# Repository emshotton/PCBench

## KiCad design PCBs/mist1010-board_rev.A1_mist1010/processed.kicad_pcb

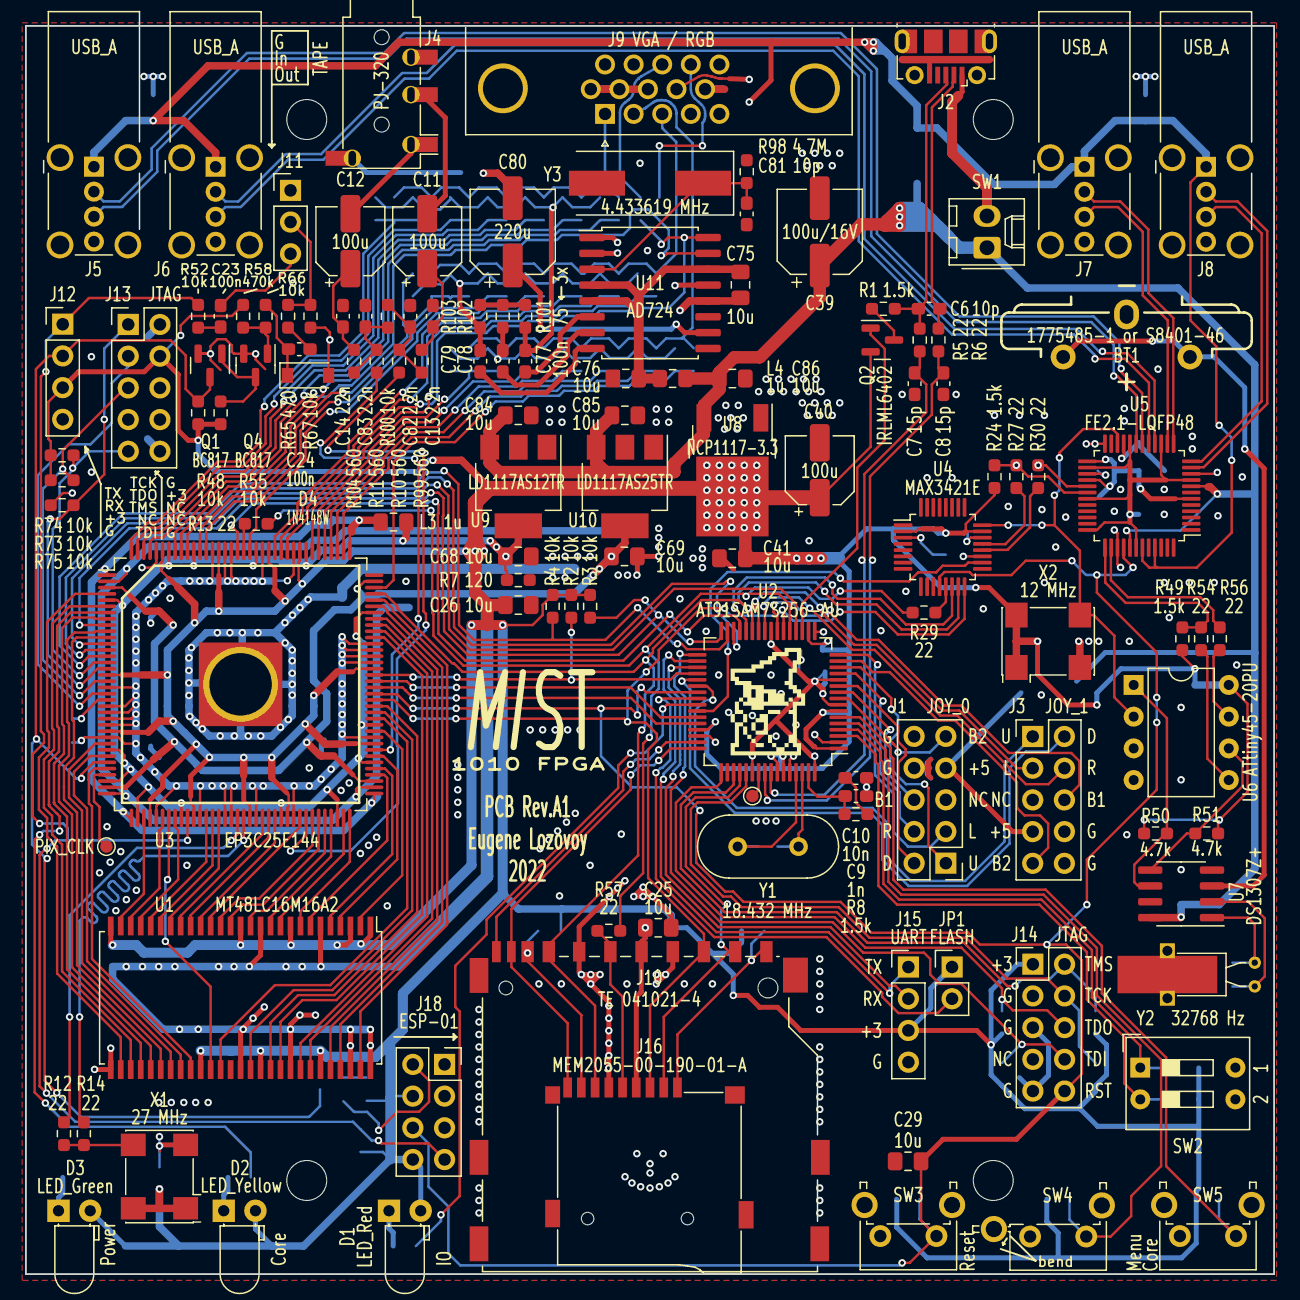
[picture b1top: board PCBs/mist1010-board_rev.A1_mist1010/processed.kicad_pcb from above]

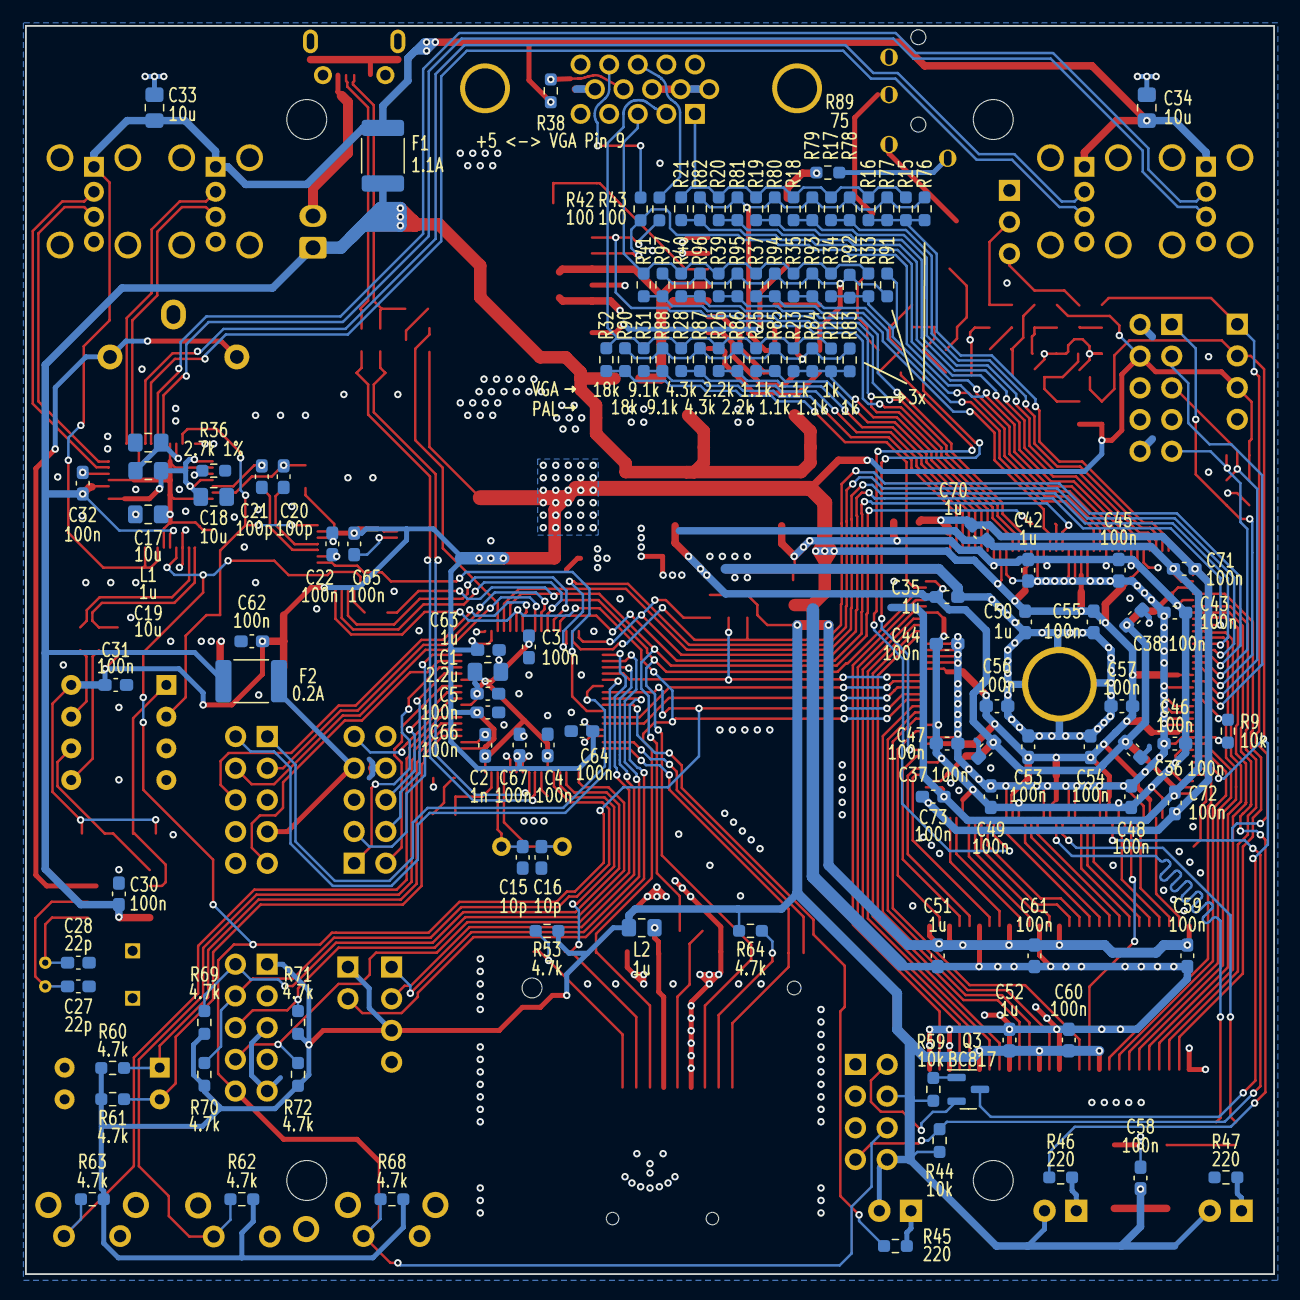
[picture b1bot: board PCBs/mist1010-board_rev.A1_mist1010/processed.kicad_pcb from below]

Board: 2 copper layers, 100.0 x 100.0 mm, 250 parts (123 on the bottom side), 202 nets.

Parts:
BT1: 1775485-1 or S8401-46; CR2032V
C1: 2.2u; C_0805_2012Metric_Pad1.18x1.45mm_HandSolder
C2, C9: 1n; C_0603_1608Metric_Pad1.08x0.95mm_HandSolder
C3, C4, C5, C22, C23, C24, C30, C31, C32, C36, C37, C38, C43, C44, C45, C46, C47, C48, C49, C53, C54, C55, C56, C57, C58, C59, C60, C61, C62, C64, C65, C66, C67, C71, C72, C73, C77, C78, C79: 100n; C_0603_1608Metric_Pad1.08x0.95mm_HandSolder
C6, C15, C16, C81: 10p; C_0603_1608Metric_Pad1.08x0.95mm_HandSolder
C7, C8: 15p; C_0603_1608Metric_Pad1.08x0.95mm_HandSolder
C10: 10n; C_0603_1608Metric_Pad1.08x0.95mm_HandSolder
C11, C12, C40: 100u; CP_Elec_5x5.9
C13, C14, C82, C83: 2.2n; C_0603_1608Metric_Pad1.08x0.95mm_HandSolder
C17, C18, C19, C25, C26, C29, C33, C34, C41, C68, C69, C75, C76, C84, C85, C86: 10u; C_0805_2012Metric_Pad1.18x1.45mm_HandSolder
C20, C21: 100p; C_0603_1608Metric_Pad1.08x0.95mm_HandSolder
C27, C28: 22p; C_0603_1608Metric_Pad1.08x0.95mm_HandSolder
C35, C42, C50, C51, C52, C63, C70: 1u; C_0603_1608Metric_Pad1.08x0.95mm_HandSolder
C39: 100u/16V; CP_Elec_6.3x7.7
C80: 220u; CP_Elec_6.3x7.7
D1: LED_Red; LED_D3.0mm_Horizontal_O1.27mm_Z6.0mm
D2: LED_Yellow; LED_D3.0mm_Horizontal_O1.27mm_Z6.0mm
D3: LED_Green; LED_D3.0mm_Horizontal_O1.27mm_Z6.0mm
D4: 1N4148W; D_SOD-123
F1: 1.1A; Fuse_1812_4532Metric_Pad1.30x3.40mm_HandSolder
F2: 0.2A; Fuse_1812_4532Metric_Pad1.30x3.40mm_HandSolder
H1, H2, H3, H4: Screw M3 dk=5mm L=4mm; MountingHole_3.2mm_M3_dk5.2mm
J1, J3, J13, J14: Conn_02x05_Odd_Even; PinHeader_2x05_P2.54mm_Vertical
J2: USB_B_Micro; USB_Micro-B_Molex-105017-0001
J4: PJ-320; PJ-320A_D
J5, J6, J7, J8: USB_A; USB_A_Wuerth_614004134726_Horizontal
J9: DB15_Female_HighDensity_MountingHoles; DSUB-15-HD_Female_Horizontal_P2.29x1.98mm_EdgePinOffset3.03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
J10: TE 041021-4; SD_TE_2041021-mod
J11: PJ392; PinHeader_1x03_P2.54mm_Vertical
J12, J15: Conn_01x04; PinHeader_1x04_P2.54mm_Vertical
J16: MEM2055-00-190-01-A; GCT-MEM2055-00-190-01-A
J18: ESP-01; PinSocket_2x04_P2.54mm_Vertical
JP1: Jumper_2_Open; PinHeader_1x02_P2.54mm_Vertical
L1, L2, L3, L4: 1u; L_0805_2012Metric_Pad1.15x1.40mm_HandSolder
LOGO1: graphic; black-mage-6.7x9.5
Q1, Q3, Q4: BC817; SOT-23
Q2: IRLML6402; SOT-23
R1, R8, R24, R49: 1.5k; R_0603_1608Metric_Pad0.98x0.95mm_HandSolder
R2, R3, R4, R9, R44, R48, R52, R55, R59, R66, R67, R73, R74, R75, R100: 10k; R_0603_1608Metric_Pad0.98x0.95mm_HandSolder
R5, R6, R12, R13, R14, R27, R29, R30, R54, R56, R57: 22; R_0603_1608Metric_Pad0.98x0.95mm_HandSolder
R7: 120; R_0603_1608Metric_Pad0.98x0.95mm_HandSolder
R10, R11, R99, R104: 560; R_0603_1608Metric_Pad0.98x0.95mm_HandSolder
R15, R22, R33, R76, R83, R91: 1k; R_0603_1608Metric_Pad0.98x0.95mm_HandSolder
R16, R17, R23, R25, R34, R35, R77, R78, R84, R85, R92, R93: 1.1k; R_0603_1608Metric_Pad0.98x0.95mm_HandSolder
R18, R26, R37, R79, R86, R94: 2.2k; R_0603_1608Metric_Pad0.98x0.95mm_HandSolder
R19, R28, R39, R80, R87, R95: 4.3k; R_0603_1608Metric_Pad0.98x0.95mm_HandSolder
R20, R31, R40, R81, R88, R96: 9.1k; R_0603_1608Metric_Pad0.98x0.95mm_HandSolder
R21, R32, R41, R82, R90, R97: 18k; R_0603_1608Metric_Pad0.98x0.95mm_HandSolder
R36: 2.7k 1%; R_0603_1608Metric_Pad0.98x0.95mm_HandSolder
R38: 0; R_0603_1608Metric_Pad0.98x0.95mm_HandSolder
R42, R43: 100; R_0603_1608Metric_Pad0.98x0.95mm_HandSolder
R45, R46, R47: 220; R_0603_1608Metric_Pad0.98x0.95mm_HandSolder
R50, R51, R53, R60, R61, R62, R63, R64, R68, R69, R70, R71, R72: 4.7k; R_0603_1608Metric_Pad0.98x0.95mm_HandSolder
R58: 470k; R_0603_1608Metric_Pad0.98x0.95mm_HandSolder
R65: 470; R_0603_1608Metric_Pad0.98x0.95mm_HandSolder
R89, R101, R102, R103: 75; R_0603_1608Metric_Pad0.98x0.95mm_HandSolder
R98: 4.7M; R_0603_1608Metric_Pad0.98x0.95mm_HandSolder
SW1: PB05A; Molex_KK-254_AE-6410-02A_1x02_P2.54mm_Vertical
SW2: SW_DIP_x02; SW_DIP_SPSTx02_Slide_9.78x7.26mm_W7.62mm_P2.54mm
SW3, SW4, SW5: SW_Push; SW_Tactile_SPST_Angled_PTS645Vx58-2LFS
TP1, TP2: TestPoint; TestPoint_Pad_D1.0mm
U1: MT48LC16M16A2; TSOP-II-54_22.2x10.16mm_P0.8mm
U2: AT91SAM7S256-AU; TQFP-64_10x10mm_P0.5mm
U3: EP3C25E144; ALTERA-QFP-145
U4: MAX3421E; LQFP-32_5x5mm_P0.5mm
U5: FE2.1-LQFP48; LQFP-48_7x7mm_P0.5mm
U6: ATtiny45-20PU; DIP-8_W7.62mm
U7: DS1307Z+; SOIC-8_3.9x4.9mm_P1.27mm
U8: NCP1117-3.3; TO-252-2
U9: LD1117AS12TR; SOT-223-3_TabPin2
U10: LD1117AS25TR; SOT-223-3_TabPin2
U11: AD724; SOIC-16W_7.5x10.3mm_P1.27mm
X1: 27 MHz; Oscillator_SMD_SeikoEpson_SG8002CA-4Pin_7.0x5.0mm
X2: 12 MHz; Oscillator_SMD_SeikoEpson_SG8002CA-4Pin_7.0x5.0mm
Y1: 18.432 MHz; Crystal_HC49-U_Vertical
Y2: 32768 Hz; Crystal_C38-LF_D3.0mm_L8.0mm_Horizontal_1EP_style2
Y3: 4.433619 MHz; Crystal_SMD_HC49-SD

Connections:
+1V2: C42.2, C43.2, C44.2, C45.2, C46.2, C47.2, C48.2, C49.2, C68.2, L3.1, R7.1, U3.5 (VCCINT), U3.29 (VCCINT), U3.34 (VCCINT), U3.38 (VCCINT), U3.45 (VCCINT), U3.61 (VCCINT), U3.70 (VCCINT), U3.78 (VCCINT), U3.84 (VCCINT), U3.102 (VCCINT), U3.116 (VCCINT), U3.124 (VCCINT), U3.134 (VCCINT), U3.138 (VCCINT), U9.2 (VO)
+1V2_PLL: C70.2, C71.2, C72.2, C73.2, L3.2, U3.1 (VCCD_PLL3), U3.37 (VCCD_PLL1), U3.73 (VCCD_PLL4), U3.109 (VCCD_PLL2)
+2V5: C35.2, C36.2, C37.2, C38.2, C69.2, U3.3 (VCCA3), U3.35 (VCCA1), U3.75 (VCCA4), U3.107 (VCCA2), U10.2 (VO)
+3V3: C26.2, C31.2, C40.1, C41.2, C50.2, C51.2, C52.2, C53.2, C54.2, C55.2, C56.2, C57.2, C58.2, C59.2, C60.2, C61.2, C62.2, C63.2, C64.2, C65.2, C66.2, C67.2, D1.2 (A), D2.2 (A), D3.2 (A), J12.3, J13.4, J14.1, J15.3, J18.4, J18.8, JP1.1 (A), L2.1, Q2.2 (S), R2.1, R3.1, R4.1, R24.1, R44.1, R48.2, R49.1, R50.1, R51.1, R53.1, R55.2, R58.2, R59.1, R60.1, R61.1, R62.1, R63.1, R64.1, R68.1, R69.1, R70.1, R71.1, R72.1, R73.1, R74.1, U1.1 (VDD), U1.3 (VDDQ), U1.9 (VDDQ), U1.14 (VDD), U1.27 (VDD), U1.37 (CKE), U1.43 (VDDQ), U1.49 (VDDQ), U2.1 (ADVREF), U2.7 (VDDIN), U2.18 (VDDIO), U2.45 (VDDIO), U2.58 (VDDIO), U2.59 (VDDFLASH), U3.17 (VCCIO1), U3.26 (VCCIO2), U3.40 (VCCIO3), U3.47 (VCCIO3), U3.56 (VCCIO4), U3.62 (VCCIO4), U3.81 (VCCIO5), U3.93 (VCCIO6), U3.117 (VCCIO7), U3.122 (VCCIO7), U3.130 (VCCIO8), U3.139 (VCCIO8), U4.2 (VL), U4.23 (VCC), U6.8 (VCC), U8.2 (VO), X1.1 (EN), X1.4 (V+), X2.1 (EN), X2.4 (V+)
+5V: C30.2, C32.2, C39.1, C84.2, C85.2, C86.2, F1.1, F2.1, L4.1, SW1.1 (A), U5.8 (VDD5), U5.41 (VBUSM), U7.8 (VCC), U8.3 (VI), U9.3 (VI), U10.3 (VI)
+5V_JOY: F2.2, J1.7, J3.7
+5V_PAL: C75.2, C76.2, L4.2, U11.4 (AVCC), U11.5 (ENCD), U11.14 (DVCC)
+5V_USB: C33.2, C34.2, F1.2, J5.1 (VBUS), J6.1 (VBUS), J7.1 (VBUS), J8.1 (VBUS), R38.1, U5.43 (OVCJ5), U5.45 (OVCJ1)
+BATT: BT1.1 (+), U7.3 (VBAT)
/ARM_TCK: J14.4, R70.2, U2.53 (TCK)
/ARM_TDI: J14.8, R72.2, U2.33 (TDI)
/ARM_TDO: J14.6, R71.2, U2.49 (TDO)
/ARM_TMS: J14.2, R69.2, U2.51 (TMS)
/AUDIO_L: R10.1, U3.65 (IO/VREFB4N0)
/AUDIO_R: R11.1, U3.80 (IO/VREFB5N0)
/B: J9.3, R33.2, R34.2, R35.2, R37.2, R39.2, R40.2, R41.2
/Button1: R62.2, SW4.1, U2.5 (AD6)
/Button2: R63.2, SW5.1, U2.6 (AD7)
/CLK_12: U4.24 (XI), U5.22 (XIN), U6.2 (XTAL1/PB3), X2.3 (OUT)
/CLK_27: R12.1, R14.1, X1.3 (OUT)
/CONF_DATA0: U2.30 (PA9/PGMM1), U3.13 (IO/DATA0)
/CONF_DCLK: U2.20 (PA15/PGMD3), U3.12 (DCLK)
/CONF_DONE: R2.2, U2.36 (PA4/PGMNCMD), U3.92 (CONF_DONE)
/CONF_NCONFIG: R4.2, U2.31 (PA8/PGMM0), U3.14 (nCONFIG)
/CONF_NSTATUS: R3.2, U2.32 (PA7/PGMNVALID), U3.9 (nSTATUS)
/Composite: J4.S, R89.1
/DM_PUP: Q2.1 (G), U2.19 (PA16/PGMD4)
/FPGA_TCK: J13.1, R75.1, U3.16 (TCK)
/FPGA_TDI: J13.9, R74.2, U3.15 (TDI)
/FPGA_TDO: J13.3, U3.20 (TDO)
/FPGA_TMS: J13.5, R73.2, U3.18 (TMS)
/G: J9.2, R22.2, R23.2, R25.2, R26.2, R28.2, R31.2, R32.2
/HS: J9.13, R43.2
/MISO: J10.7 (DAT0), J16.7 (DAT0), U2.27 (PA12/PGMD0), U3.105 (IO/VREFB6N0), U4.15 (MISO)
/MOSI: J10.2 (CMD), J16.3 (CMD), U2.22 (PA13/PGMD1), U3.88 (CLK7/DIFFCLK_3n), U4.16 (MOSI)
/PIXEL_CLK: TP1.1, U3.33 (IO/RDN1)
/R: J9.1, R15.2, R16.2, R17.2, R18.2, R19.2, R20.2, R21.2
/RAM_A0: U1.23 (A0), U3.49 (IO/DIFFIO_B9n/DQ1B)
/RAM_A1: U1.24 (A1), U3.44 (IO/PLL1_CLKOUTn)
/RAM_A2: U1.25 (A2), U3.42 (IO/DQS1B/CQ1B#/CDPCLK2)
/RAM_A3: U1.26 (A3), U3.39 (IO/DIFFIO_B2p)
/RAM_A4: U1.29 (A4), U3.4 (IO)
/RAM_A5: U1.30 (A5), U3.6 (IO/DIFFIO_L3n/DATA1/ASDO)
/RAM_A6: U1.31 (A6), U3.8 (IO/DIFFIO_L4p/FLASH_nCE/nCSO)
/RAM_A7: U1.32 (A7), U3.10 (IO/DIFFIO_L6p/DQS0L/CQ1L/DPCLK0)
/RAM_A8: U1.33 (A8), U3.11 (IO/DIFFIO_L6n)
/RAM_A9: U1.34 (A9), U3.28 (IO/DIFFIO_L8p)
/RAM_A10: U1.22 (A10), U3.50 (IO/DIFFIO_B10n/DQ1B)
/RAM_A11: U1.35 (A11), U3.30 (IO/DIFFIO_L11p/DQS1L/CQ1L#/DPCLK1)
/RAM_A12: U1.36 (A12), U3.32 (IO/RUP1)
/RAM_BA0: U1.20 (BA0), U3.58 (IO/DIFFIO_B16p/DQ1B)
/RAM_BA1: U1.21 (BA1), U3.51 (IO/DIFFIO_B11p/DQ1B)
/RAM_CLK: U1.38 (CLK), U3.43 (IO/PLL1_CLKOUTp)
/RAM_DQ0: U1.2 (DQ0), U3.83 (IO/DIFFIO_R11p)
/RAM_DQ1: U1.4 (DQ1), U3.79 (IO/DIFFIO_R13n)
/RAM_DQ2: U1.5 (DQ2), U3.77 (IO/RDN3)
/RAM_DQ3: U1.7 (DQ3), U3.76 (IO/RUP3)
/RAM_DQ4: U1.8 (DQ4), U3.72 (IO/PLL4_CLKOUTn)
/RAM_DQ5: U1.10 (DQ5), U3.71 (IO/PLL4_CLKOUTp)
/RAM_DQ6: U1.11 (DQ6), U3.69 (IO/DIFFIO_B24p)
/RAM_DQ7: U1.13 (DQ7), U3.68 (IO/DIFFIO_B23n/DQS0B/CQ1B/CDPCLK3)
/RAM_DQ8: U1.42 (DQ8), U3.86 (IO/DIFFIO_R9n/DEV_OE)
/RAM_DQ9: U1.44 (DQ9), U3.87 (IO/DIFFIO_R9p/DEV_CLRn)
/RAM_DQ10: U1.45 (DQ10), U3.98 (IO/DIFFIO_R5n/INIT_DONE)
/RAM_DQ11: U1.47 (DQ11), U3.99 (IO/DIFFIO_R5p/CRC_ERROR)
/RAM_DQ12: U1.48 (DQ12), U3.100 (IO)
/RAM_DQ13: U1.50 (DQ13), U3.101 (IO/DIFFIO_R4n/nCEO)
/RAM_DQ14: U1.51 (DQ14), U3.103 (IO/DIFFIO_R4p/CLKUSR)
/RAM_DQ15: U1.53 (DQ15), U3.104 (IO/DQS0R/CQ1R/DPCLK7)
/RAM_DQMH: U1.39 (DQMH), U3.85 (IO/DIFFIO_R10p/DQS1R/CQ1R#/DPCLK6)
/RAM_DQML: U1.15 (DQML), U3.67 (IO/RDN2/DQ1B)
/RST: C29.2, J14.10, J18.6, R68.2, SW3.1, U2.39 (NRST), U3.89 (CLK6/DIFFCLK_3p), U4.12 (RES), U5.40 (XRSTJ)
/RTC_DN: R49.2, R54.2, U5.37 (DM7)
/RTC_DP: R56.2, U5.38 (DP7)
/RX_ARM: J15.2, U2.35 (PA5/PGMRDY)
/RX_FPGA: J12.2, Q1.3 (C), Q3.3 (C), R48.1, U3.31 (IO/VREFB2N0)
/SCK: R13.2, R29.1, R57.1, U2.21 (PA14/PGMD2)
/SD_CD: J10.10 (CARD_DETECT), J16.9 (DET_B), U2.48 (PA0/PGMEN0)
/SD_CLK: J10.5 (CLK), J16.5 (CLK), R57.2
/SD_DAT1: J10.8 (DAT1), J16.8 (DAT1), R64.2
/SD_DAT2: J10.9 (DAT2), J16.1 (DAT2), R53.2
/SD_VDD: C25.2, J10.4 (VDD), J16.4 (VDD), L2.2
/SD_WP: J10.11 (WRITE_PROTECT), U2.47 (PA1/PGMEN1)
/SS0: U2.28 (PA11/PGMM3), U4.14 (SS)
/SS1: J10.1 (CD/DAT3), J16.2 (DAT3/CD), U2.52 (PA31)
/SS2/FPGA: U2.29 (PA10/PGMM2), U3.127 (CLK9/DIFFCLK_5p)
/SS3/OSD: U2.43 (PA3), U3.91 (CLK4/DIFFCLK_2p)
/SS4/SD_DIRECT: U2.44 (PA2/PGMEN2), U3.90 (CLK5/DIFFCLK_2n)
/Switch1: R60.2, SW2.1, U2.4 (AD5)
/Switch2: R61.2, SW2.2, U2.3 (AD4)
/TAPE_IN: J11.2, R65.1, R67.1
/TAPE_OUT: C23.1, J11.3
/TX_ARM: J15.1, U2.34 (PA6/PGMNOE)
/TX_FPGA: J12.1, J18.7, R44.2, R52.1, U3.46 (IO/VREFB3N0)
/UDN: C6.2, J2.2 (D-), R6.1
/UDP: C6.1, J2.3 (D+), R1.2, R5.1
/USBHUB1_DN: J5.2 (D-), U5.18 (DM1)
/USBHUB1_DP: J5.3 (D+), U5.19 (DP1)
/USBHUB2_DN: J6.2 (D-), U5.16 (DM2)
/USBHUB2_DP: J6.3 (D+), U5.17 (DP2)
/USBHUB3_DN: J7.2 (D-), U5.13 (DM3)
/USBHUB3_DP: J7.3 (D+), U5.14 (DP3)
/USBHUB4_DN: J8.2 (D-), U5.11 (DM4)
/USBHUB4_DP: J8.3 (D+), U5.12 (DP4)
/USBH_INT: U2.42 (PA30), U4.18 (INT)
/USB_DN: C8.1, R6.2, U2.56 (DDM)
/USB_DP: C7.1, R5.2, U2.57 (DDP)
/VGA_B0: R41.1, R97.1, U3.115 (IO/RDN4/DQ1T)
/VGA_B1: R40.1, R96.1, U3.120 (IO/DIFFIO_T19n/PADD1/DQ1T)
/VGA_B2: R39.1, R95.1, U3.121 (IO/DIFFIO_T17p/PADD4)
/VGA_B3: R37.1, R94.1, U3.125 (IO/DIFFIO_T13p/PADD12)
/VGA_B4: R35.1, R93.1, U3.132 (IO/DIFFIO_T10n/DATA2/DQ1T)
/VGA_B5: R33.1, R34.1, R91.1, R92.1, U3.133 (IO/DIFFIO_T10p/DATA3/DQ1T)
/VGA_G0: R32.1, R90.1, U3.106 (IO/DIFFIO_R1n/PADD20)
/VGA_G1: R31.1, R88.1, U3.110 (IO/DIFFIO_T23p/DQS0T/CQ1T/CDPCLK6)
/VGA_G2: R28.1, R87.1, U3.111 (IO/DIFFIO_T22p)
/VGA_G3: R26.1, R86.1, U3.112 (IO/PLL2_CLKOUTn)
/VGA_G4: R25.1, R85.1, U3.113 (IO/PLL2_CLKOUTp)
/VGA_G5: R22.1, R23.1, R83.1, R84.1, U3.114 (IO/RUP4/DQ1T)
/VGA_HS: R43.1, U3.119 (IO/VREFB7N0), U11.16 (HSYNC)
/VGA_R0: R21.1, R82.1, U3.135 (IO/DIFFIO_T9p/DATA4/DQ1T)
/VGA_R1: R20.1, R81.1, U3.137 (IO/DATA5/DQ1T)
/VGA_R2: R19.1, R80.1, U3.141 (IO/DIFFIO_T2p)
/VGA_R3: R18.1, R79.1, U3.142 (IO/DATA12/DQS1T/CQ1T#/CDPCLK7)
/VGA_R4: R17.1, R78.1, U3.143 (IO/PLL3_CLKOUTn/DQ1T)
/VGA_R5: R15.1, R16.1, R76.1, R77.1, U3.144 (IO/PLL3_CLKOUTp/DM1T)
/VGA_VS: R42.1, U3.136 (IO/VREFB8N0), U11.15 (VSYNC)
/VS: J9.14, R42.2
/~JOY0_B1: J1.6, U2.10 (PA18/PGMD6/AD1)
/~JOY0_B2: J1.9, U2.9 (PA17/PGMD5/AD0)
/~JOY0_DOWN: J1.2, U2.11 (PA21/PGMD9)
/~JOY0_LEFT: J1.3, U2.16 (PA20/PGMD8/AD3)
/~JOY0_RIGHT: J1.4, U2.13 (PA19/PGMD7/AD2)
/~JOY0_UP: J1.1, U2.14 (PA22/PGMD10)
/~JOY1_B1: J3.6, U2.23 (PA24/PGMD12)
/~JOY1_B2: J3.9, U2.15 (PA23/PGMD11)
/~JOY1_DOWN: J3.2, U2.37 (PA27/PGMD15)
/~JOY1_LEFT: J3.3, U2.26 (PA26/PGMD14)
/~JOY1_RIGHT: J3.4, U2.25 (PA25/PGMD13)
/~JOY1_UP: J3.1, U2.38 (PA28)
/~LED_ARM: R45.2, U2.41 (PA29)
/~LED_FPGA: R46.2, U3.7 (IO/VREFB1N0)
/~RAM_CAS: U1.17 (~CAS), U3.64 (IO)
/~RAM_CS: U1.19 (~CS), U3.59 (IO/DIFFIO_B17p/DQ1B)
/~RAM_RAS: U1.18 (~RAS), U3.60 (IO/DIFFIO_B17n/DQ1B)
/~RAM_WE: U1.16 (~WE), U3.66 (IO/RUP2/DQ1B)
GND: BT1.2 (-), C1.1, C2.1, C3.1, C4.1, C5.1, C7.2, C8.2, C9.2, C10.2, C13.2, C14.2, C15.2, C16.2, C17.1, C18.1, C19.1, C20.2, C21.2, C22.1, C25.1, C26.1, C27.2, C28.2, C29.1, C30.1, C31.1, C32.1, C33.1, C34.1, C35.1, C36.1, C37.1, C38.1, C39.2, C40.2, C41.1, C42.1, C43.1, C44.1, C45.1, C46.1, C47.1, C48.1, C49.1, C50.1, C51.1, C52.1, C53.1, C54.1, C55.1, C56.1, C57.1, C58.1, C59.1, C60.1, C61.1, C62.1, C63.1, C64.1, C65.1, C66.1, C67.1, C68.1, C69.1, C70.1, C71.1, C72.1, C73.1, C75.1, C76.1, C81.2, C82.2, C83.2, C84.1, C85.1, C86.1, D4.2 (A), J1.8, J1.10, J2.5 (GND), J2.6 (Shield), J3.8, J3.10, J4.R2, J5.4 (GND), J5.5 (Shield), J6.4 (GND), J6.5 (Shield), J7.4 (GND), J7.5 (Shield), J8.4 (GND), J8.5 (Shield), J9.0, J9.5, J9.6, J9.7, J9.8, J9.10, J10.3 (VSS), J10.6 (VSS), J10.12 (SHELL1), J10.13 (SHELL2), J11.1, J12.4, J13.2, J13.10, J14.3, J14.5, J14.9, J15.4, J16.6 (VSS), J16.10 (DET_A), J16.11 (SHIELD), J18.1, Q1.2 (E), Q4.2 (E), R7.2, R9.1, R36.2, R47.2, R67.2, R75.2, R98.1, R101.2, R102.2, R103.2, SW2.3, SW2.4, SW3.2, SW4.2, SW5.2, U1.6 (GNDQ), U1.12 (GNDQ), U1.28 (GND), U1.41 (GND), U1.46 (GNDQ), U1.52 (GNDQ), U1.54 (GND), U2.2 (GND), U2.17 (GND), U2.46 (GND), U2.60 (GND), U3.2 (GNDA3), U3.19 (GND), U3.22 (CLK0/DIFFCLK_0p), U3.23 (CLK1/DIFFCLK_0n), U3.24 (CLK2/DIFFCLK_1p), U3.25 (CLK3/DIFFCLK_1n), U3.27 (GND), U3.36 (GNDA1), U3.41 (GND), U3.48 (GND), U3.52 (CLK15/DIFFCLK_6p), U3.53 (CLK14/DIFFCLK_6n), U3.57 (GND), U3.63 (GND), U3.74 (GNDA4), U3.82 (GND), U3.94 (MSEL0), U3.95 (GND), U3.96 (MSEL1), U3.97 (MSEL2), U3.108 (GNDA2), U3.118 (GND), U3.123 (GND), U3.128 (CLK10/DIFFCLK_4n), U3.129 (CLK11/DIFFCLK_4p), U3.131 (GND), U3.140 (GND), U3.145 (PAD), U4.3 (GND), U4.19 (GND), U5.10 (VSS), U5.24 (VS_PLL), U5.39 (VSS), U6.4 (GND), U7.4 (GND), U8.1 (GND), U9.1 (GND), U10.1 (GND), U11.1 (STDN), U11.2 (AGND), U11.12 (SELECT), U11.13 (DGND), X1.2 (GND), X2.2 (GND), Y2.3, Y3.2
unnamed: C1.2, C2.2, C3.2, C4.2, C5.2, U2.8 (VDDOUT), U2.12 (VDDCORE), U2.24 (VDDCORE), U2.54 (VDDCORE), U2.64 (VDDPLL)
unnamed: C9.1, R8.2, U2.63 (PLLRC)
unnamed: C10.1, R8.1
unnamed: C11.1, C13.1, R99.2
unnamed: C11.2, J4.R1
unnamed: C12.1, C14.1, R104.2
unnamed: C12.2, J4.T
unnamed: C15.1, U2.62 (XIN/PGMCK), Y1.1
unnamed: C16.1, U2.61 (XOUT), Y1.2
unnamed: C17.2, L1.2, U5.21 (VD_PLL)
unnamed: C18.2, L1.1, U5.6 (VD18), U5.25 (VD18_O), U5.28 (VD18)
unnamed: C19.2, U5.9 (VDD3_O), U5.15 (VD33), U5.20 (VD33), U5.26 (VD33), U5.31 (VD33), U5.36 (VD33), U5.42 (VD33)
unnamed: C20.1, R24.2, R27.2, U5.30 (DPU)
unnamed: C21.1, R30.2, U5.29 (DMU)
unnamed: C22.2, U4.22 (VBCOMP)
unnamed: C23.2, R52.2
unnamed: C24.1, D4.1 (K), R66.1
unnamed: C24.2, R65.2
unnamed: C27.1, U7.2 (X2), Y2.2
unnamed: C28.1, U7.1 (X1), Y2.1
unnamed: C77.1, U11.6 (RIN)
unnamed: C77.2, R76.2, R77.2, R78.2, R79.2, R80.2, R81.2, R82.2, R101.1
unnamed: C78.1, U11.7 (GIN)
unnamed: C78.2, R83.2, R84.2, R85.2, R86.2, R87.2, R88.2, R90.2, R102.1
unnamed: C79.1, U11.8 (BIN)
unnamed: C79.2, R91.2, R92.2, R93.2, R94.2, R95.2, R96.2, R97.2, R103.1
unnamed: C80.1, U11.10 (COMP)
unnamed: C80.2, R89.2
unnamed: C81.1, R98.2, U11.3 (FIN), Y3.1
unnamed: C82.1, R10.2, R99.1, R100.1
unnamed: C83.1, R11.2, R100.2, R104.1
unnamed: D1.1 (K), R45.1
unnamed: D2.1 (K), R46.1
unnamed: D3.1 (K), R47.1
unnamed: J2.1 (VBUS), SW1.2 (B)
unnamed: J9.9, R38.2
unnamed: J18.2, Q3.2 (E)
unnamed: JP1.2 (B), U2.40 (TST)
unnamed: Q1.1 (B), Q4.3 (C), R55.1
unnamed: Q2.3 (D), R1.1
unnamed: Q3.1 (B), R59.2
unnamed: Q4.1 (B), R58.1, R66.2
unnamed: R9.2, U3.21 (nCE)
unnamed: R12.2, U3.54 (CLK13/DIFFCLK_7p)
unnamed: R13.1, U3.126 (CLK8/DIFFCLK_5n)
unnamed: R14.2, U3.55 (CLK12/DIFFCLK_7n)
unnamed: R27.1, U4.21 (D+)
unnamed: R29.2, U4.13 (SCK)
unnamed: R30.1, U4.20 (D-)
unnamed: R36.1, U5.27 (REXT)
unnamed: R50.2, U6.1 (~RESET/PB5), U7.6 (SCL)
unnamed: R51.2, U6.6 (PB1), U7.5 (SDA)
unnamed: R54.1, U6.5 (AREF/PB0)
unnamed: R56.1, U6.7 (PB2)
unnamed: TP2.1, U2.55 (ERASE)

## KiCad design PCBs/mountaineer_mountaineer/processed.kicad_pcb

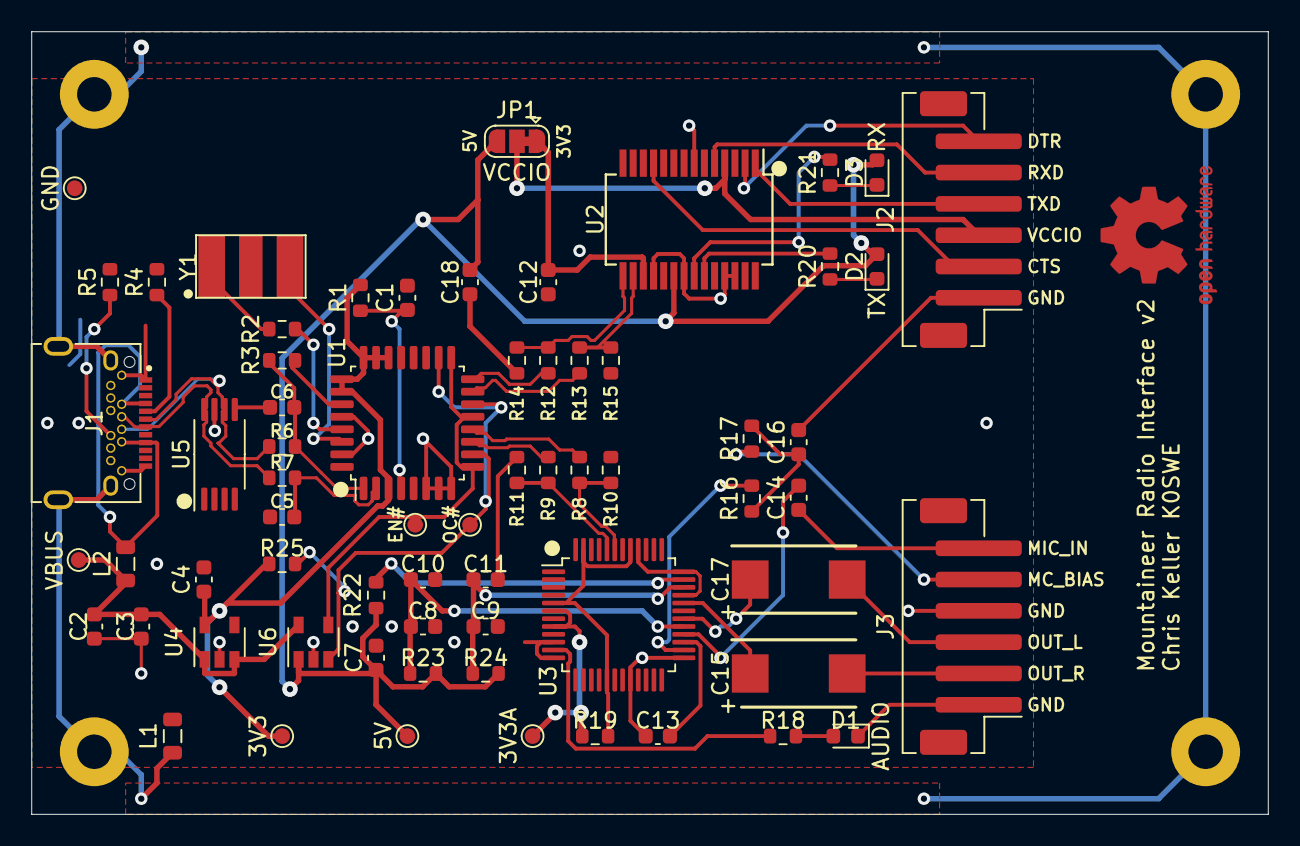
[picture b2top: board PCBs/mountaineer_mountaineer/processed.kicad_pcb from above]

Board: 2 copper layers, 79.0 x 50.0 mm, 71 parts (0 on the bottom side), 54 nets.

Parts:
C1, C3, C7, C10, C11, C12, C18: 0.1uF; C_0603_1608Metric
C2, C4, C8, C9, C13, C16: 4.7uF; C_0603_1608Metric
C5, C6: 22pF; C_0603_1608Metric
C14: 1uF; C_0603_1608Metric
C15, C17: 470uF; CAPPM7343X430N
D1: AUDIO; LED_0603_1608Metric
D2: TX; LED_0603_1608Metric
D3: RX; LED_0603_1608Metric
H1, H2, H3, H4: MountingHole_Pad; MountingHole_2.2mm_M2_Pad
J1: USB_C_Receptacle; CUI_UJ31-CH-G-SMT-TR-67
J2: CAT; JST_PH_B6B-PH-SM4-TB_1x06-1MP_P2.00mm_Vertical
J3: AUDIO; JST_PH_B6B-PH-SM4-TB_1x06-1MP_P2.00mm_Vertical
JP1: VCCIO; SolderJumper-3_P1.3mm_Bridged12_RoundedPad1.0x1.5mm
L1, L2: FB; L_0805_2012Metric
LOGO1: Logo_Open_Hardware_Small; OSHW-Logo2_9.8x8mm_Copper
R1, R10, R11, R14, R15, R19, R25: 15k; R_0603_1608Metric
R2, R3: 1.5k; R_0603_1608Metric
R4, R5: 5.1k; R_0603_1608Metric
R6, R7, R8, R9, R12, R13: 27R; R_0603_1608Metric
R16: 2.2k; R_0603_1608Metric
R17: 1.2k; R_0603_1608Metric
R18: 68R; R_0603_1608Metric
R20, R21: 150R; R_0603_1608Metric
R22, R23, R24: 0R; R_0603_1608Metric
TP1: VBUS; TestPoint_Pad_D1.0mm
TP2: GND; TestPoint_Pad_D1.0mm
TP3: 3V3; TestPoint_Pad_D1.0mm
TP4: 3V3A; TestPoint_Pad_D1.0mm
TP5: OC#; TestPoint_Pad_D1.0mm
TP6: 5V; TestPoint_Pad_D1.0mm
TP7: EN#; TestPoint_Pad_D1.0mm
U1: TUSB2036; LQFP-32_7x7mm_P0.8mm
U2: FT232RL; SSOP-28_5.3x10.2mm_P0.65mm
U3: HS-100B; LQFP-48_7x7mm_P0.5mm
U4: TPS76333; SOT-23-5
U5: SN75240; TSSOP-8_4.4x3mm_P0.65mm
U6: TPS2041; SOT-23-5
Y1: AWSCR-6.00CPLA; AWSCR600CPLAC30T4

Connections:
+3V3: C4.1, R1.2, R25.1, TP3.1, U1.3, U1.22, U1.23, U1.24, U1.25, U1.26, U4.5
+5V: C7.1, C18.1, D2.2, D3.2, JP1.3, R22.2, R23.2, R24.2, TP6.1, U2.20, U6.1
/3V3A: R19.1, TP4.1, U3.6, U3.8
/3V3U: C12.1, JP1.1, U2.17
/AUDIO_L: C17.2, J3.3
/AUDIO_R: C15.2, J3.2
/AVDD1: C8.1, C10.1, R23.1, U3.29
/AVDD2: C9.1, C11.1, R24.1, U3.34
/CTS: J2.2, U2.11
/D0+: C6.1, R3.2, R6.1, U1.1
/D0-: C5.1, R7.1, U1.2
/D1+: R8.2, U1.12
/D1-: R9.2, U1.11
/D2+: R12.2, U1.16
/D2-: R13.2, U1.15
/DP0PUR: R3.1, U1.27
/DR+: J1.A6, J1.B6, R6.2, U5.6
/DR-: J1.A7, J1.B7, R7.2, U5.8
/DTR: J2.6, U2.2
/DVDD: R22.1, U3.35
/EN#: TP7.1, U1.9, U1.13, U1.17, U6.4
/HIDPU: R19.2, U3.5, U3.17, U3.41, U3.47
/LEDO: R18.2, U3.11
/LOL: C17.1, U3.30
/LOR: C15.1, U3.32
/MICIN: C14.2, U3.28
/MIC_BIAS: J3.5, R17.1
/MIC_IN: C14.1, J3.6
/OC#: R25.2, TP5.1, U1.10, U1.14, U1.18, U6.3
/RESET#: C1.1, R1.1, U1.4
/RXD: J2.5, U2.5
/RXLED: R21.2, U2.22
/TXD: J2.4, U2.1
/TXLED: R20.2, U2.23
/U1+: R8.1, R10.1, U3.43
/U1-: R9.1, R11.1, U3.44
/U2+: R12.1, R14.1, U2.15
/U2-: R13.1, R15.1, U2.16
/VBIAS: R16.2, U3.26
/VCCIO: J2.3, JP1.2, U2.4
/VREF: C13.2, U3.27
/XTAL1: U1.30, Y1.3
/XTAL2: R2.2, U1.29
GND1: H1.1, H2.1, H3.1, H4.1, J1.S1, L1.1
GNDREF: C1.2, C2.2, C3.2, C4.2, C5.2, C6.2, C7.2, C8.2, C9.2, C10.2, C11.2, C12.2, C13.1, C16.2, C18.2, D1.1, J1.A1, J1.A12, J1.B1, J1.B12, J2.1, J3.1, J3.4, L1.2, R4.2, R5.2, R10.2, R11.2, R14.2, R15.2, TP2.1, U1.6, U1.7, U1.8, U1.21, U1.28, U1.31, U2.7, U2.18, U2.21, U2.25, U2.26, U3.10, U3.12, U3.20, U3.25, U3.33, U3.36, U3.40, U4.2, U5.5, U5.7, U6.2, Y1.2
unnamed: C16.1, R16.1, R17.2
unnamed: D1.2, R18.1
unnamed: D2.1, R20.1
unnamed: D3.1, R21.1
unnamed: J1.A4, J1.A9, J1.B4, J1.B9, L2.1
unnamed: J1.A5, R4.1
unnamed: J1.B5, R5.1
unnamed: R2.1, Y1.1
VBUS: C2.1, C3.1, L2.2, TP1.1, U4.1, U4.3, U6.5

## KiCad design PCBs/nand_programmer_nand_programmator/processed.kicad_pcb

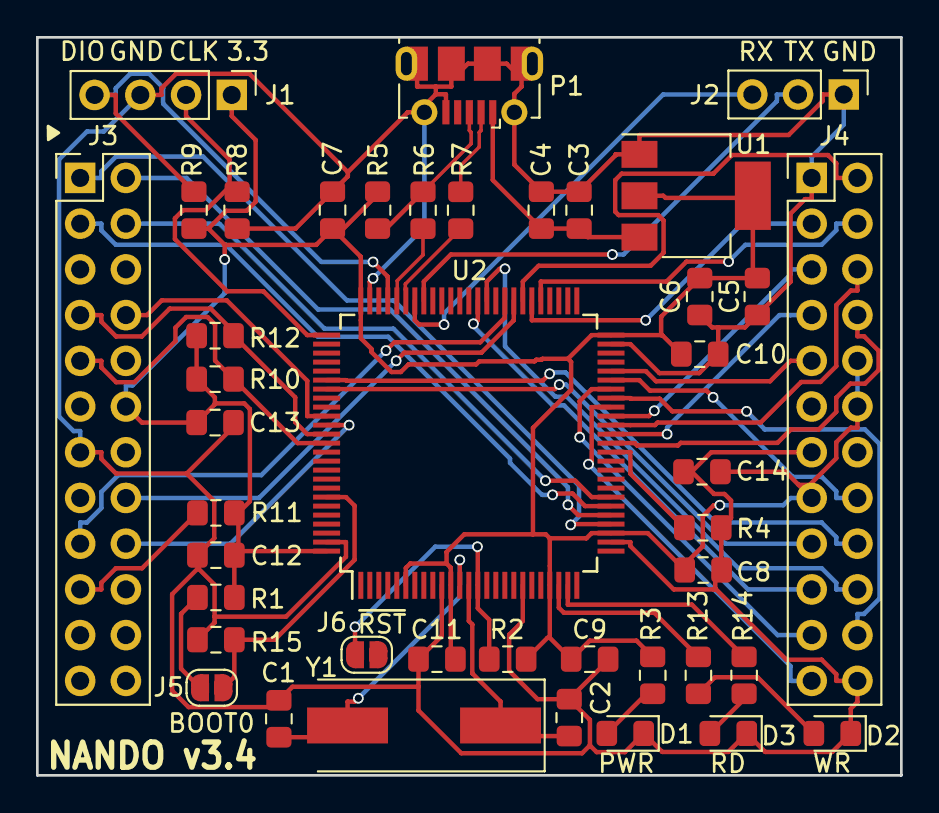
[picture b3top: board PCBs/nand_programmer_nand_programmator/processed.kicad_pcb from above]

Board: 2 copper layers, 48.0 x 41.0 mm, 42 parts (0 on the bottom side), 49 nets.

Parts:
C1, C2: 30pF; C_0805_2012Metric_Pad1.15x1.40mm_HandSolder
C3, C6: 10uF; C_0805_2012Metric_Pad1.15x1.40mm_HandSolder
C4, C5, C7, C8, C9, C10, C11, C12, C13, C14: 0.1uF; C_0805_2012Metric_Pad1.15x1.40mm_HandSolder
D1: GREEN; LED_0805_2012Metric_Pad1.15x1.40mm_HandSolder
D2: RED; LED_0805_2012Metric_Pad1.15x1.40mm_HandSolder
D3: YELLOW; LED_0805_2012Metric_Pad1.15x1.40mm_HandSolder
J1: Conn_01x04; PinHeader_1x04_P2.54mm_Vertical
J2: Conn_01x03; PinHeader_1x03_P2.54mm_Vertical
J3: Conn_02x12_Odd_Even_Left; PinHeader_2x12_P2.54mm_Vertical
J4: Conn_02x12_Odd_Even_Right; PinHeader_2x12_P2.54mm_Vertical_2
J5: BOOT0; SolderJumper-2_P1.3mm_Open_RoundedPad1.0x1.5mm
J6: ~{RST}; SolderJumper-2_P1.3mm_Open_RoundedPad1.0x1.5mm
P1: USB; USB_Micro-B_Molex-105017-0001
R1: 510; R_0805_2012Metric_Pad1.15x1.40mm_HandSolder
R2, R4, R8, R9, R10, R11, R12, R15: 10k; R_0805_2012Metric_Pad1.15x1.40mm_HandSolder
R3, R13, R14: 1k; R_0805_2012Metric_Pad1.15x1.40mm_HandSolder
R5: 1.5k; R_0805_2012Metric_Pad1.15x1.40mm_HandSolder
R6, R7: 22; R_0805_2012Metric_Pad1.15x1.40mm_HandSolder
U1: LM1117-3.3; SOT-223
U2: STM32F103VCT6; LQFP-100_14x14mm_Pitch0.5mm
Y1: Crystal_SMD_8MHz_18pF; Crystal_SMD_HC49-SD

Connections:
+3V3: C5.1, C6.1, C7.1, C8.1, C9.1, C10.1, C11.1, C12.1, C13.2, C14.2, J1.1, J3.12, J4.34, J4.37, J4.39, R1.1, R2.1, R3.2, R5.2, R9.1, R10.2, R11.2, R12.1, U1.2, U1.4, U2.6, U2.11, U2.22, U2.28, U2.50, U2.75, U2.100
+5V: C3.1, C4.1, P1.1, U1.3
/BOOT0: J5.1, R15.2, U2.94
/FSMC_ALE: J3.17, U2.59
/FSMC_CLE: J3.16, U2.58
/FSMC_D0: J4.29, U2.61
/FSMC_D1: J4.30, U2.62
/FSMC_D2: J4.31, U2.81
/FSMC_D3: J4.32, U2.82
/FSMC_D4: J4.41, U2.38
/FSMC_D5: J4.42, U2.39
/FSMC_D6: J4.43, U2.40
/FSMC_D7: J4.44, U2.41
/FSMC_D8: J4.26, U2.42
/FSMC_D9: J4.27, U2.43
/FSMC_D10: J4.28, U2.44
/FSMC_D11: J4.33, U2.45
/FSMC_D12: J4.40, U2.46
/FSMC_D13: J4.45, U2.55
/FSMC_D14: J4.46, U2.56
/FSMC_D15: J4.47, U2.57
/FSMC_NCE2: J3.9, R10.1, U2.88
/FSMC_NOE: J3.8, U2.85
/FSMC_NWAIT: J3.7, R12.2, U2.87
/FSMC_NWE: J3.18, U2.86
/NRST: J6.2, R2.2, U2.14
/RED: R13.2, U2.23
/SPI1_MISO: J3.3, U2.31
/SPI1_MOSI: J3.4, U2.32
/SPI1_NSS: J3.1, U2.29
/SPI1_SCK: J3.2, U2.30
/SWCLK: J1.2, R8.2, U2.76
/SWDIO: J1.4, R9.2, U2.72
/USART1_RX: J2.3, U2.69
/USART1_TX: J2.2, U2.68
/USB_DN: R7.1, U2.70
/USB_DP: R6.1, U2.71
/USB_N: P1.2, R7.2
/USB_P: P1.3, R5.1, R6.2
/YELLOW: R14.2, U2.24
GNDD: C1.2, C2.2, C3.2, C4.2, C5.2, C6.2, C7.2, C8.2, C9.2, C10.2, C11.2, C12.2, C13.1, C14.1, D1.1, D2.1, D3.1, J1.3, J2.1, J3.13, J4.25, J4.36, J4.48, J6.1, P1.5, P1.6, R4.1, R8.1, R15.1, U1.1, U2.10, U2.19, U2.27, U2.49, U2.74, U2.99
unnamed: C1.1, U2.12, Y1.2
unnamed: C2.1, U2.13, Y1.1
unnamed: D1.2, R3.1
unnamed: D2.2, R13.1
unnamed: D3.2, R14.1
unnamed: J3.19, R11.1
unnamed: J5.2, R1.2
unnamed: R4.2, U2.37

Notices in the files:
PCBs/mountaineer_mountaineer/processed.kicad_pcb:
Licensed under Creative Commons CC-BY-4.0
